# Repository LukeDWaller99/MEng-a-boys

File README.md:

## Contributions
**Luke Waller**

*Authored*

**Jack Pendlebury**

*Ripping everything except the ESCs out.*

# MEng-a-boys
MEng-a-boys

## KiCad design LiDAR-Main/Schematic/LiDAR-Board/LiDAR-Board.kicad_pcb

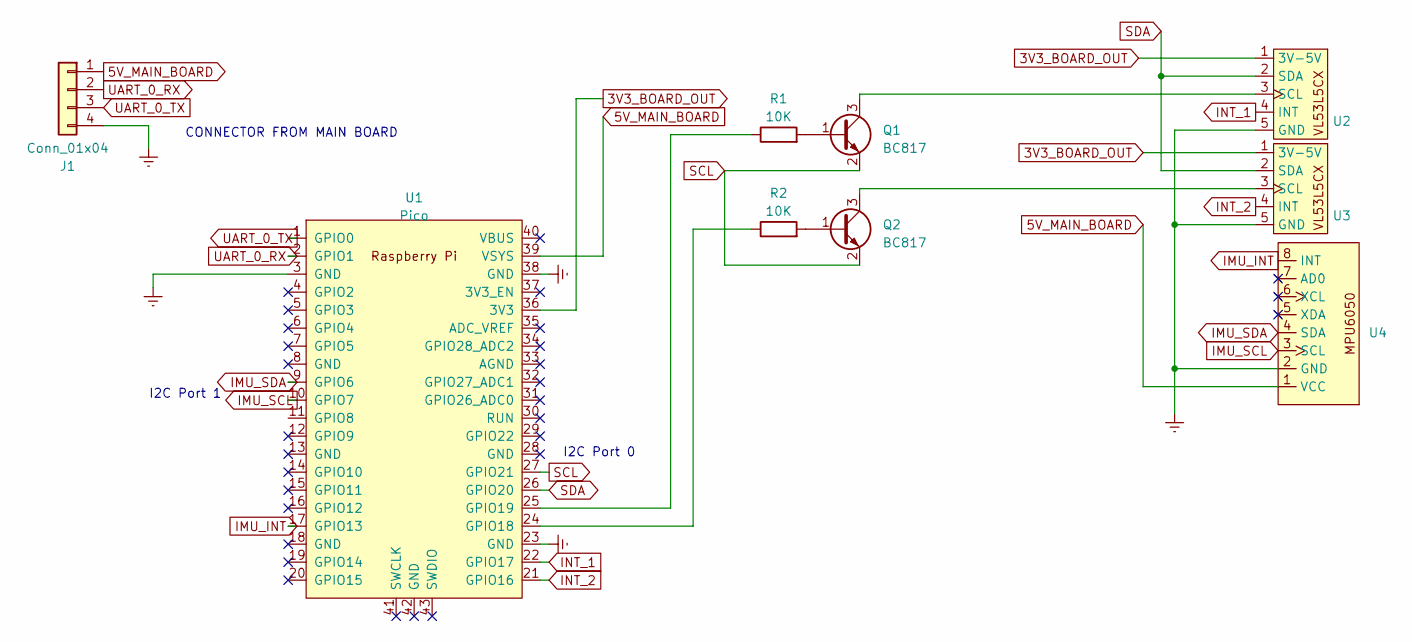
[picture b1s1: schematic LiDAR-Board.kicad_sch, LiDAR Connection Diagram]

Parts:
J1: Conn_01x04; Conn_01x04_MOLEX
Q1, Q2: BC817; SOT-23
R1, R2: 10K; R_0603_1608Metric
U1: Pico; Pi_Pico
U2, U3, U4: Conn_01x05_MOLEX

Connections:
3V3_BOARD_OUT: U1.36 (3V3), U2.1 (3V-5V), U3.1 (3V-5V)
5V_MAIN_BOARD: J1.1, U1.39 (VSYS), U4.1 (VCC)
Earth: J1.4, U1.3 (GND), U1.23 (GND), U1.38 (GND), U2.5 (GND), U3.5 (GND), U4.2 (GND)
IMU_INT: U1.17 (GPIO13), U4.8 (INT)
IMU_SCL: U1.10 (GPIO7), U4.3 (SCL)
IMU_SDA: U1.9 (GPIO6), U4.4 (SDA)
INT_1: U1.22 (GPIO17), U2.4 (INT)
INT_2: U1.21 (GPIO16), U3.4 (INT)
unnamed: Q1.1 (B), R1.2
unnamed: Q1.3 (C), U2.3 (SCL)
unnamed: Q2.1 (B), R2.2
unnamed: Q2.3 (C), U3.3 (SCL)
unnamed: R2.1, U1.24 (GPIO18)
unnamed: R1.1, U1.25 (GPIO19)
SCL: Q1.2 (E), Q2.2 (E), U1.27 (GPIO21)
SDA: U1.26 (GPIO20), U2.2 (SDA), U3.2 (SDA)
UART_0_RX: J1.2, U1.2 (GPIO1)
UART_0_TX: J1.3, U1.1 (GPIO0)

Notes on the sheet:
CONNECTOR FROM MAIN BOARD
I2C Port 1
I2C Port 0

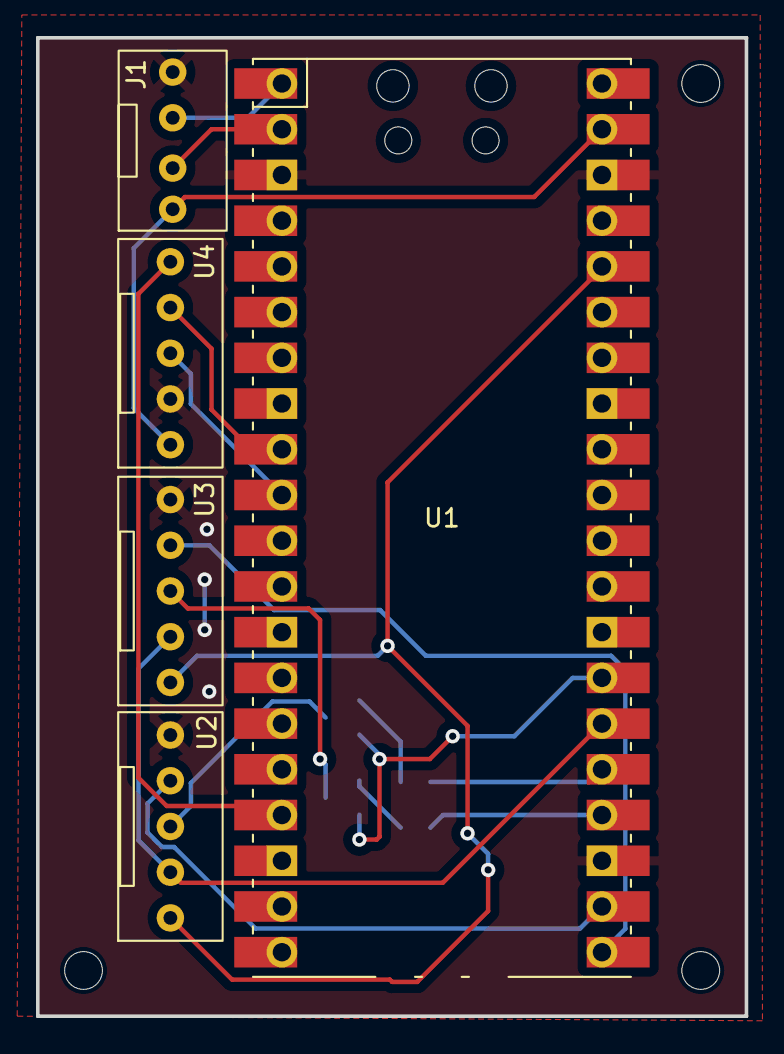
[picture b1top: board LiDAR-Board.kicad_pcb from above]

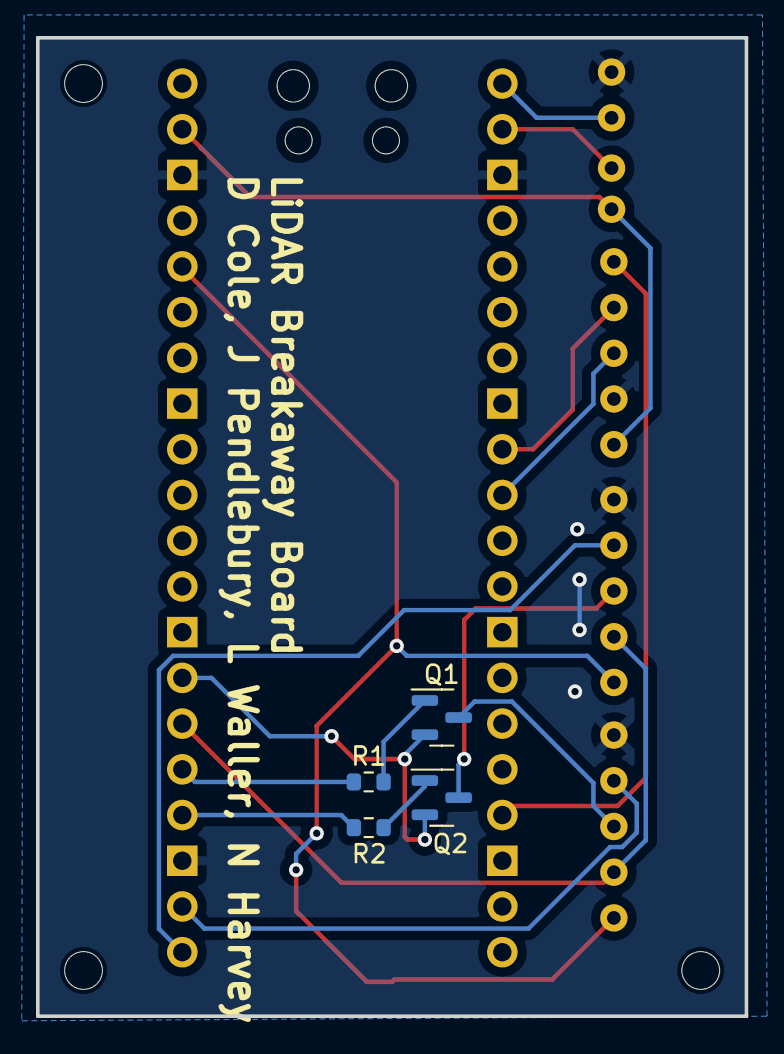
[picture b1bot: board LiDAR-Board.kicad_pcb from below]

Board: 2 copper layers, 39.4 x 54.4 mm, 9 parts (4 on the bottom side), 18 nets.

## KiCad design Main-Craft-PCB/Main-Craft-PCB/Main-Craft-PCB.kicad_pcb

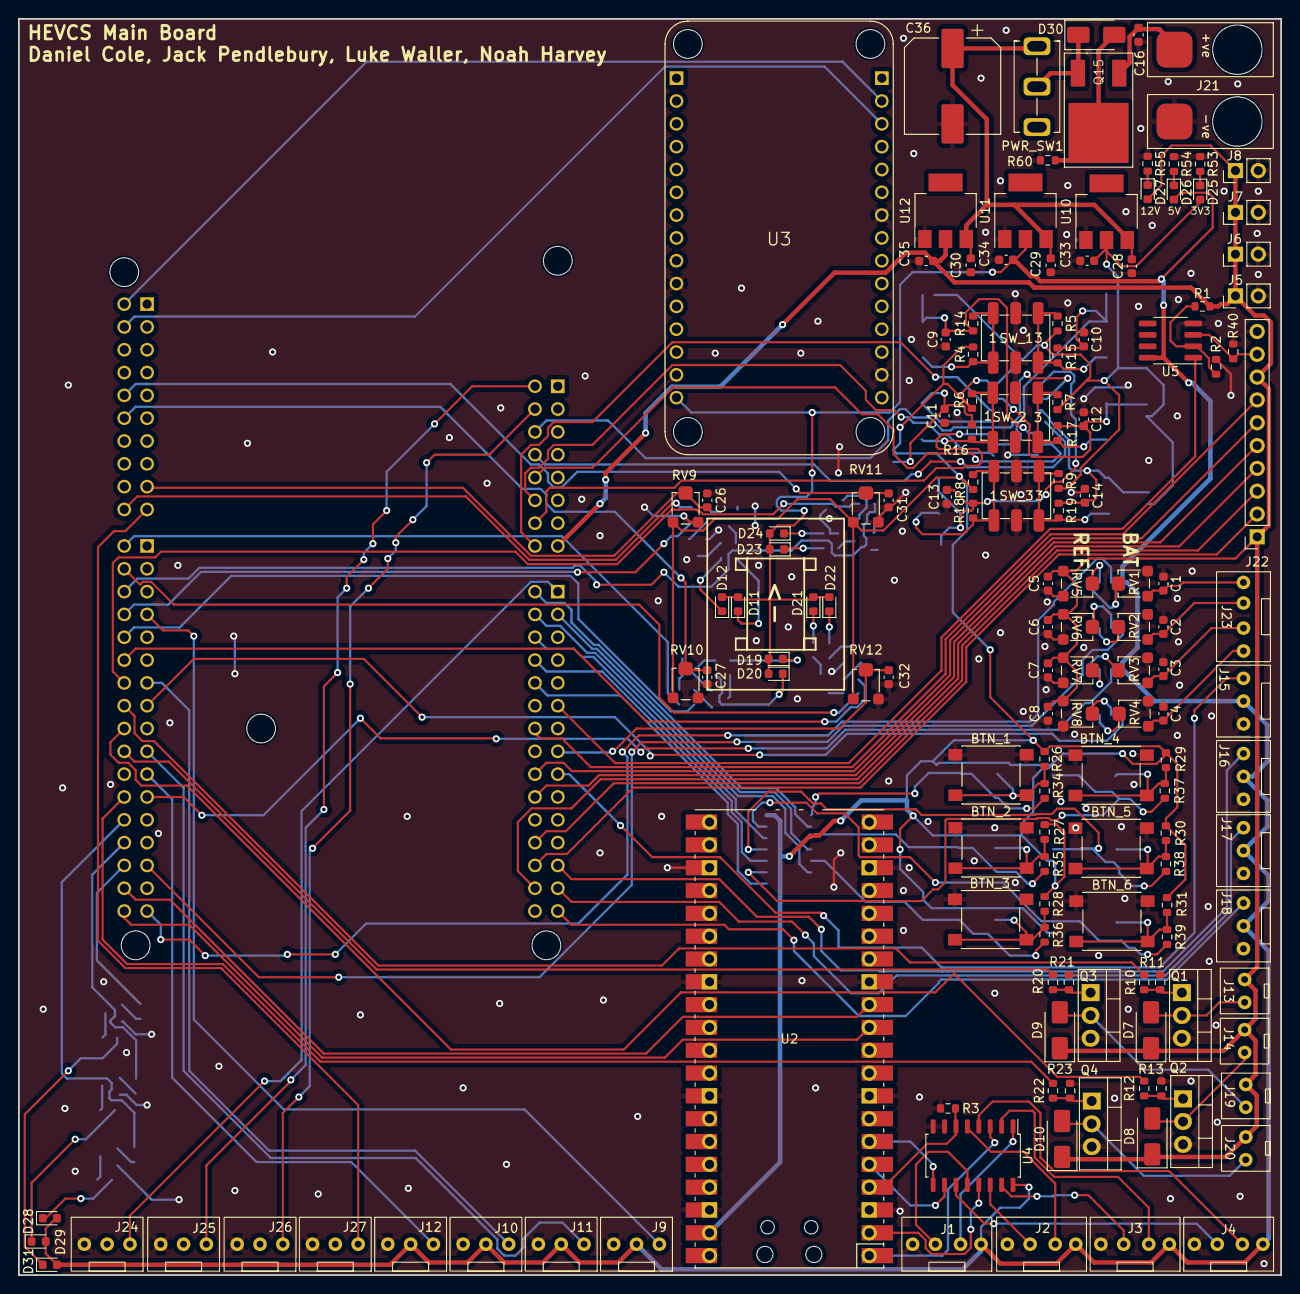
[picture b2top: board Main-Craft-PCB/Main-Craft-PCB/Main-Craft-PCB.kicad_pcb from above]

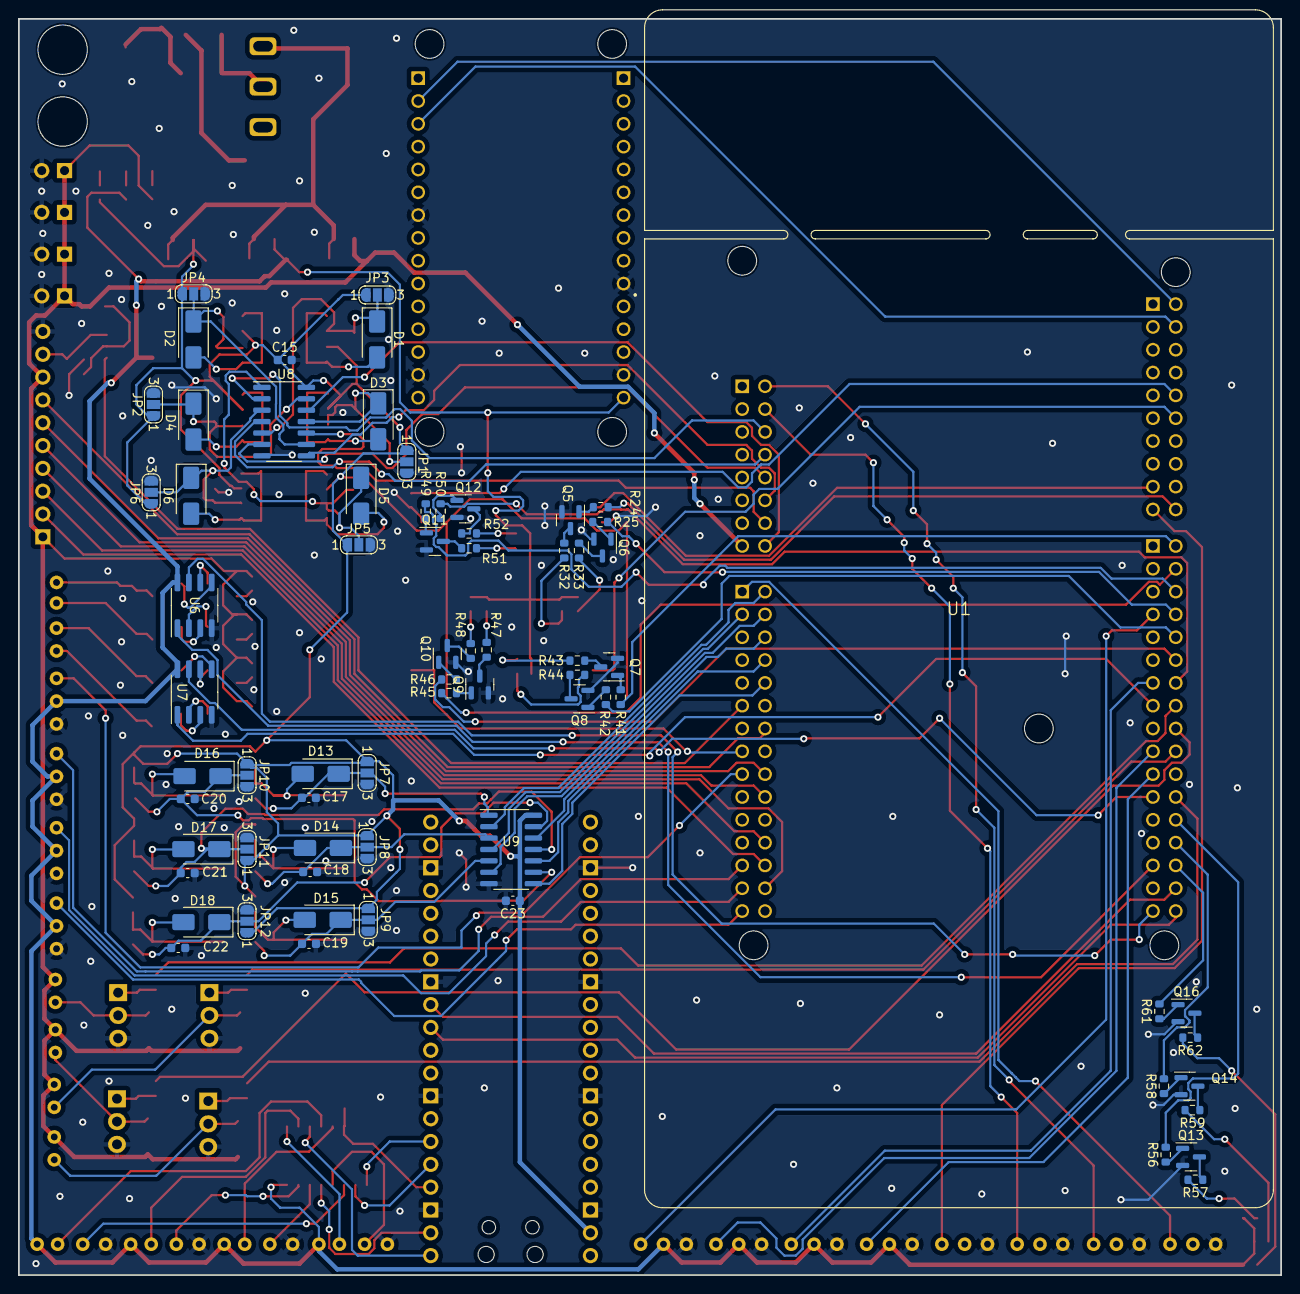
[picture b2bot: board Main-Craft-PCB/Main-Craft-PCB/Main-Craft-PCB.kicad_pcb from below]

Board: 2 copper layers, 140.5 x 139.8 mm, 216 parts (70 on the bottom side), 107 nets.

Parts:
BTN_1, BTN_2, BTN_3, BTN_4, BTN_5, BTN_6: SW_SPST; SW_Push_1P1T_NO_6x6mm_H9.5mm
C1, C2, C3, C4, C5, C6, C7, C8, C9, C10, C11, C12, C13, C14, C15, C16, C17, C18, C19, C20, C21, C22, C23, C26, C27, C28, C29, C30, C31, C32, C33, C34, C35: 100nF; C_0603_1608Metric
C36: 470uF; CP_Elec_10x10.5
D1, D2, D3, D4, D5, D6, D7, D8, D9, D10, D13, D14, D15, D16, D17, D18, D30: D; D_SMA
D11, D12, D19, D20, D21, D22, D23, D24, D27: RED; LED_0603_1608Metric
D25, D29: YELLOW; LED_0603_1608Metric
D26, D31: BLUE; LED_0603_1608Metric
D28: GREEN; LED_0603_1608Metric
J1: UART_1; Conn_01x04_MOLEX
J2: UART_2; Conn_01x04_MOLEX
J3: UART_3; Conn_01x04_MOLEX
J4: UART_4; Conn_01x04_MOLEX
J5, J6, J7, J8: LEDS; PinHeader_1x02_P2.54mm_Vertical
J9: S500_1; Conn_01x03_MOLEX
J10: S500_2; Conn_01x03_MOLEX
J11: S500_3; Conn_01x03_MOLEX
J12: S500_4; Conn_01x03_MOLEX
J13: SOL_1; Conn_01x02_MOLEX
J14: SOL_2; Conn_01x02_MOLEX
J15: RELAY_1; Conn_01x03_MOLEX
J16: RELAY_2; Conn_01x03_MOLEX
J17, J18: RELAY_3; Conn_01x03_MOLEX
J19: SOL_3; Conn_01x02_MOLEX
J20: SOL_4; Conn_01x02_MOLEX
J21: PWR_IN; 12AWG_PWR_IN
J22: Conn_01x10; PinSocket_1x10_P2.54mm_Vertical
J23: BAT_IN; Conn_01x04_MOLEX
J24: VESC_1; Conn_01x03_MOLEX
J25: VESC_2; Conn_01x03_MOLEX
J26: VESC_3; Conn_01x03_MOLEX
J27: VESC_4; Conn_01x03_MOLEX
JP1, JP2, JP3, JP4, JP5, JP6: JP; SolderJumper-3_P1.3mm_Open_RoundedPad1.0x1.5mm_NumberLabels
JP7, JP8, JP9, JP10, JP11, JP12: SolderJumper_3_Open; SolderJumper-3_P1.3mm_Open_RoundedPad1.0x1.5mm_NumberLabels
PWR_SW1: SW_SPDT; KNX-1-D1
Q1, Q2, Q3, Q4: TIP120; TO-220-3_Vertical
Q5, Q6, Q7, Q8, Q9, Q10, Q11, Q12, Q13, Q14, Q16: BC817; SOT-23
Q15: IRFR9014PBF; STD20NF06L
R1, R2, R54, R57, R62: 1K; R_0603_1608Metric
R3: 100K; R_0603_1608Metric
R4, R5, R6, R7, R8, R9, R11, R13, R14, R15, R16, R17, R18, R19, R21, R23, R26, R27, R28, R29, R30, R31, R34, R35, R36, R37, R38, R39, R40: 47K; R_0603_1608Metric
R10, R12, R20, R22, R53, R59: 2K2; R_0603_1608Metric
R24, R25, R41, R42, R45, R46, R49, R50, R56, R58, R61: 4K7; R_0603_1608Metric
R32, R33, R43, R44, R47, R48, R51, R52, R55: 150R; R_0603_1608Metric
R60: 100R; R_0603_1608Metric
RV1, RV2, RV3, RV4, RV5, RV6, RV7, RV8, RV9, RV10, RV11, RV12: 20K; Variable_Resistor
SW_1, SW_2, SW_3: SW; JS202011SCQN
U1: NUCLEO144-F429ZI; MODULE_NUCLEO-F429ZI
U2: Pi Pico; pi_pico
U3: ESP8266; ESP-8266
U4: SN74LV4052; SOIC-16_4.55x10.3mm_P1.27mm
U5, U6, U7: LM358DR2G; SOP-8_3.76x4.96mm_P1.27mm
U8, U9: 74HC14; SO-14_3.9x8.65mm_P1.27mm
U10: ZSR330GTA; SOT-223
U11: ZLDO1117G50TA; SOT-223
U12: BFU590GX; SOT-223

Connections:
12V_INPUT: C16.1, J21.1, Q15.1 (D)
+3V3: C15.1, C23.1, C33.2, D25.2 (A), JP1.1 (A), JP2.1 (A), JP3.1 (A), JP4.1 (A), JP5.1 (A), JP6.1 (A), JP7.1 (A), JP8.1 (A), JP9.1 (A), JP10.1 (A), JP11.1 (A), JP12.1 (A), R4.2, R5.2, R6.2, R7.2, R8.2, R9.2, R26.2, R27.2, R28.2, R29.2, R30.2, R31.2, RV9.1, RV10.1, RV11.1, RV12.1, U2.39 (VSYS), U8.14 (VCC), U9.14 (VCC), U10.2 (VO)
+5V: C34.2, D11.2 (A), D12.2 (A), D19.2 (A), D20.2 (A), D21.2 (A), D22.2 (A), D23.2 (A), D24.2 (A), D26.2 (A), D28.2 (A), D29.2 (A), D31.2 (A), J1.1, J2.1, J3.1, J4.1, J9.2, J10.2, J11.2, J12.2, J15.2, J16.2, J17.2, J18.2, U3.15 (Vin), U4.16 (VCC), U5.8 (V+), U6.8 (V+), U7.8 (V+), U11.2 (VO)
+12V: C5.1, C6.1, C7.1, C8.1, C35.2, D7.1 (K), D8.1 (K), D9.1 (K), D10.1 (K), D27.2 (A), J5.1, J6.1, J7.1, J8.1, J13.1, J14.1, J19.1, J20.1, J22.1, J22.8, R1.2, RV5.1, RV6.1, RV7.1, RV8.1, U12.2 (VO)
/X0: J1.3, U4.12 (X0)
/X1: J2.3, U4.14 (X1)
/X2: J3.3, U4.15 (X2)
/X3: J4.3, U4.11 (X3)
/Y0: J1.2, U4.1 (Y0)
/Y1: J2.2, U4.5 (Y1)
/Y2: J3.2, U4.2 (Y2)
/Y3: J4.2, U4.4 (Y3)
BATT_1_IN: C4.1, J23.4, RV4.1
BATT_2_IN: C3.1, J23.3, RV3.1
BATT_3_IN: C2.1, J23.2, RV2.1
BATT_4_IN: C1.1, J23.1, RV1.1
BTN_1_SB: C17.2, D13.1 (K), JP7.2 (C), R34.1, U9.1
BTN_2_SB: C18.2, D14.1 (K), JP8.2 (C), R35.1, U9.3
BTN_3_SB: C19.2, D15.1 (K), JP9.2 (C), R36.1, U9.5
BTN_4_SB: C20.2, D16.1 (K), JP10.2 (C), R37.1, U9.9
BTN_5_SB: C21.2, D17.1 (K), JP11.2 (C), R38.1, U9.11
BTN_6_SB: C22.2, D18.1 (K), JP12.2 (C), R39.1, U9.13
CON_CONNECTION: J22.9, R40.1, U5.3 (+)
Earth: BTN_1.1 (A), BTN_2.1 (A), BTN_3.1 (A), BTN_4.1 (A), BTN_5.1 (A), BTN_6.1 (A), C1.2, C2.2, C3.2, C4.2, C5.2, C6.2, C7.2, C8.2, C9.1, C10.1, C11.1, C12.1, C13.1, C14.1, C15.2, C16.2, C17.1, C18.1, C19.1, C20.1, C21.1, C22.1, C23.2, C26.2, C27.2, C28.2, C29.2, C30.2, C31.2, C32.2, C33.1, C34.1, C35.1, C36.2, J1.4, J2.4, J3.4, J4.4, J5.2, J6.2, J7.2, J8.2, J9.3, J10.3, J11.3, J12.3, J15.3, J16.3, J17.3, J18.3, J21.2, J22.10, J24.3, J25.3, J26.3, J27.3, JP1.3 (B), JP2.3 (B), JP3.3 (B), JP4.3 (B), JP5.3 (B), JP6.3 (B), JP7.3 (B), JP8.3 (B), JP9.3 (B), JP10.3 (B), JP11.3 (B), JP12.3 (B), Q1.3 (E), Q2.3 (E), Q3.3 (E), Q4.3 (E), Q5.2 (E), Q6.2 (E), Q7.2 (E), Q8.2 (E), Q9.2 (E), Q10.2 (E), Q11.2 (E), Q12.2 (E), Q13.2 (E), Q14.2 (E), Q16.2 (E), R2.1, R3.1, R11.1, R13.1, R21.1, R23.1, R40.2, R53.1, R54.1, R55.1, R60.2, RV1.3, RV2.3, RV3.3, RV4.3, RV5.3, RV6.3, RV7.3, RV8.3, RV9.3, RV10.3, RV11.3, RV12.3, SW_1.2, SW_2.2, SW_3.2, U2.3 (GND), U2.8 (GND), U2.13 (GND), U2.18 (GND), U2.23 (GND), U2.28 (GND), U2.33 (GND), U2.38 (GND), U3.10 (GND), U3.14 (GND), U3.17 (GND), U3.24 (GND), U4.7 (GND), U4.8 (GND), U5.4 (V-), U6.4 (V-), U7.4 (V-), U8.7 (GND), U9.7 (GND), U10.1 (GND), U11.1 (GND), U12.1 (GND)
unnamed: BTN_1.2 (B), D13.2 (A), R26.1, R34.2
unnamed: BTN_2.2 (B), D14.2 (A), R27.1, R35.2
unnamed: BTN_3.2 (B), D15.2 (A), R28.1, R36.2
unnamed: BTN_4.2 (B), D16.2 (A), R29.1, R37.2
unnamed: BTN_5.2 (B), D17.2 (A), R30.1, R38.2
unnamed: BTN_6.2 (B), D18.2 (A), R31.1, R39.2
unnamed: D1.2 (A), R4.1, R14.2, SW_1.1
unnamed: D2.2 (A), R5.1, R15.2, SW_1.3
unnamed: D3.2 (A), R6.1, R16.2, SW_2.1
unnamed: D4.2 (A), R7.1, R17.2, SW_2.3
unnamed: D5.2 (A), R8.1, R18.2, SW_3.1
unnamed: D6.2 (A), R9.1, R19.2, SW_3.3
unnamed: D7.2 (A), J13.2, Q1.2 (C)
unnamed: D8.2 (A), J14.2, Q2.2 (C)
unnamed: D9.2 (A), J19.2, Q3.2 (C)
unnamed: D10.2 (A), J20.2, Q4.2 (C)
unnamed: D11.1 (K), R32.2
unnamed: D12.1 (K), R33.2
unnamed: D19.1 (K), R43.2
unnamed: D20.1 (K), R44.2
unnamed: D21.1 (K), R47.2
unnamed: D22.1 (K), R48.2
unnamed: D23.1 (K), R51.2
unnamed: D24.1 (K), R52.2
unnamed: D25.1 (K), R53.2
unnamed: D26.1 (K), R54.2
unnamed: D27.1 (K), R55.2
unnamed: D28.1 (K), R57.2
unnamed: D29.1 (K), R59.2
unnamed: D30.2 (A), Q15.2 (G), R60.1
unnamed: D30.1 (K), PWR_SW1.2 (B), Q15.3 (S)
unnamed: D31.1 (K), R62.2
unnamed: Q1.1 (B), R10.2, R11.2
unnamed: Q2.1 (B), R12.2, R13.2
unnamed: Q3.1 (B), R20.2, R21.2
unnamed: Q4.1 (B), R22.2, R23.2
unnamed: Q5.1 (B), R24.1
unnamed: Q5.3 (C), R32.1
unnamed: Q6.1 (B), R25.1
unnamed: Q6.3 (C), R33.1
unnamed: Q7.1 (B), R41.1
unnamed: Q7.3 (C), R43.1
unnamed: Q8.1 (B), R42.1
unnamed: Q8.3 (C), R44.1
unnamed: Q9.1 (B), R45.1
unnamed: Q9.3 (C), R47.1
unnamed: Q10.1 (B), R46.1
unnamed: Q10.3 (C), R48.1
unnamed: Q11.1 (B), R49.1
unnamed: Q11.3 (C), R51.1
unnamed: Q12.1 (B), R50.1
unnamed: Q12.3 (C), R52.1
unnamed: Q13.1 (B), R56.1
unnamed: Q13.3 (C), R57.1
unnamed: Q14.1 (B), R58.1
unnamed: Q14.3 (C), R59.1
unnamed: Q16.1 (B), R61.1
unnamed: Q16.3 (C), R62.1
unnamed: R1.1, R2.2, U5.2 (-)
unnamed: RV2.2, U6.3 (+)
unnamed: RV6.2, U6.2 (-)
unnamed: RV1.2, U6.5 (+)
unnamed: RV5.2, U6.6 (-)
unnamed: RV4.2, U7.3 (+)
unnamed: RV8.2, U7.2 (-)
unnamed: RV3.2, U7.5 (+)
unnamed: RV7.2, U7.6 (-)
PICO_INH: R3.2, U2.4 (GP2), U4.6 (INH)
PICO_RX: U2.2 (GP1), U4.13 (X-COM)
PICO_TX: U2.1 (GPO), U4.3 (Y-COM)
SW_1_DOWN_SB: C14.2, D6.1 (K), JP6.2 (C), R19.1, U8.3
SW_1_UP_SB: C13.2, D5.1 (K), JP5.2 (C), R18.1, U8.1
SW_2_DOWN_SB: C10.2, D2.1 (K), JP4.2 (C), R15.1, U8.9
SW_2_UP_SB: C9.2, D1.1 (K), JP3.2 (C), R14.1, U8.5
SW_3_DOWN_SB: C12.2, D4.1 (K), JP2.2 (C), R17.1, U8.13
SW_3_UP_SB: C11.2, D3.1 (K), JP1.2 (C), R16.1, U8.11
TRIM_POT_1: C26.1, RV9.2
TRIM_POT_2: C31.1, RV11.2
TRIM_POT_3: C27.1, RV10.2
TRIM_POT_4: C32.1, RV12.2
UART_EN_A: U2.5 (GP3), U4.10 (A)
UART_EN_B: U2.6 (GP4), U4.9 (B)
VIN: C28.1, C29.1, C30.1, C36.1, PWR_SW1.1 (A), U10.3 (VI), U11.3 (VI), U12.3 (VI)

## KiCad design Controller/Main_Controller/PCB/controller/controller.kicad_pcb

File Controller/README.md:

# Controller Specifications
----
## Requirements
The Controller will need to remotely control the craft with bi-directional communication. This will involve serveral design considerations including:
1. [x] Microcontroller
	1. [x] NUCELO-L432KC
2. [x] Inputs
	1. [x] 2 Analogue Joysticks
	2. [x] 4 buttons
		1. [x] 3 discreet buttons
		2. [x] Reset Button
	3. [x] 1 SPDT toggling switches
3. [x] Outputs
	1. [x] Buzzer for feedback to user
	2. [x] 1 Status LEDs
4. [ ] Power
	1. [x] Power Indicator LEDs
	2. [ ] Battery Powered
		1. [ ] 18650 Li-Po battery
		2. [ ] Battery Charger
	3. [ ] Suitable Buck Converter to supply appropriate voltages
	4. [ ] Reverse polarity protection
	5. [ ] Low voltage detection chip
	6. [x] ON/OFF power switch
5. [ ] Communication with main craft
	1. [x] RF chip (nRF24L01)
	2. [ ] Bi-directional communication
6. [ ] Case
	1. [ ] Comfortable
	2. [ ] Ergonomic 
	3. [ ] Light and easy to tranport 
	4. [ ] 3D printed
	5. [ ] Easy to use
7. [ ] PCB/Electronics
	1. [x] Schematic  
	2. [ ] PCB Layout
8. [ ] Testing
	1. [x] Testing individual assemblies on a breadboard
	2. [ ] Debugging code to test all individual components on the PCB

## Dependancies/Libraries Used

`nRF24L01P.h` Authored by Owen Edwards (c) 2010 (Modified by Luke Waller - 2022)
----
## Contributions
**Luke Waller**

*Authored*

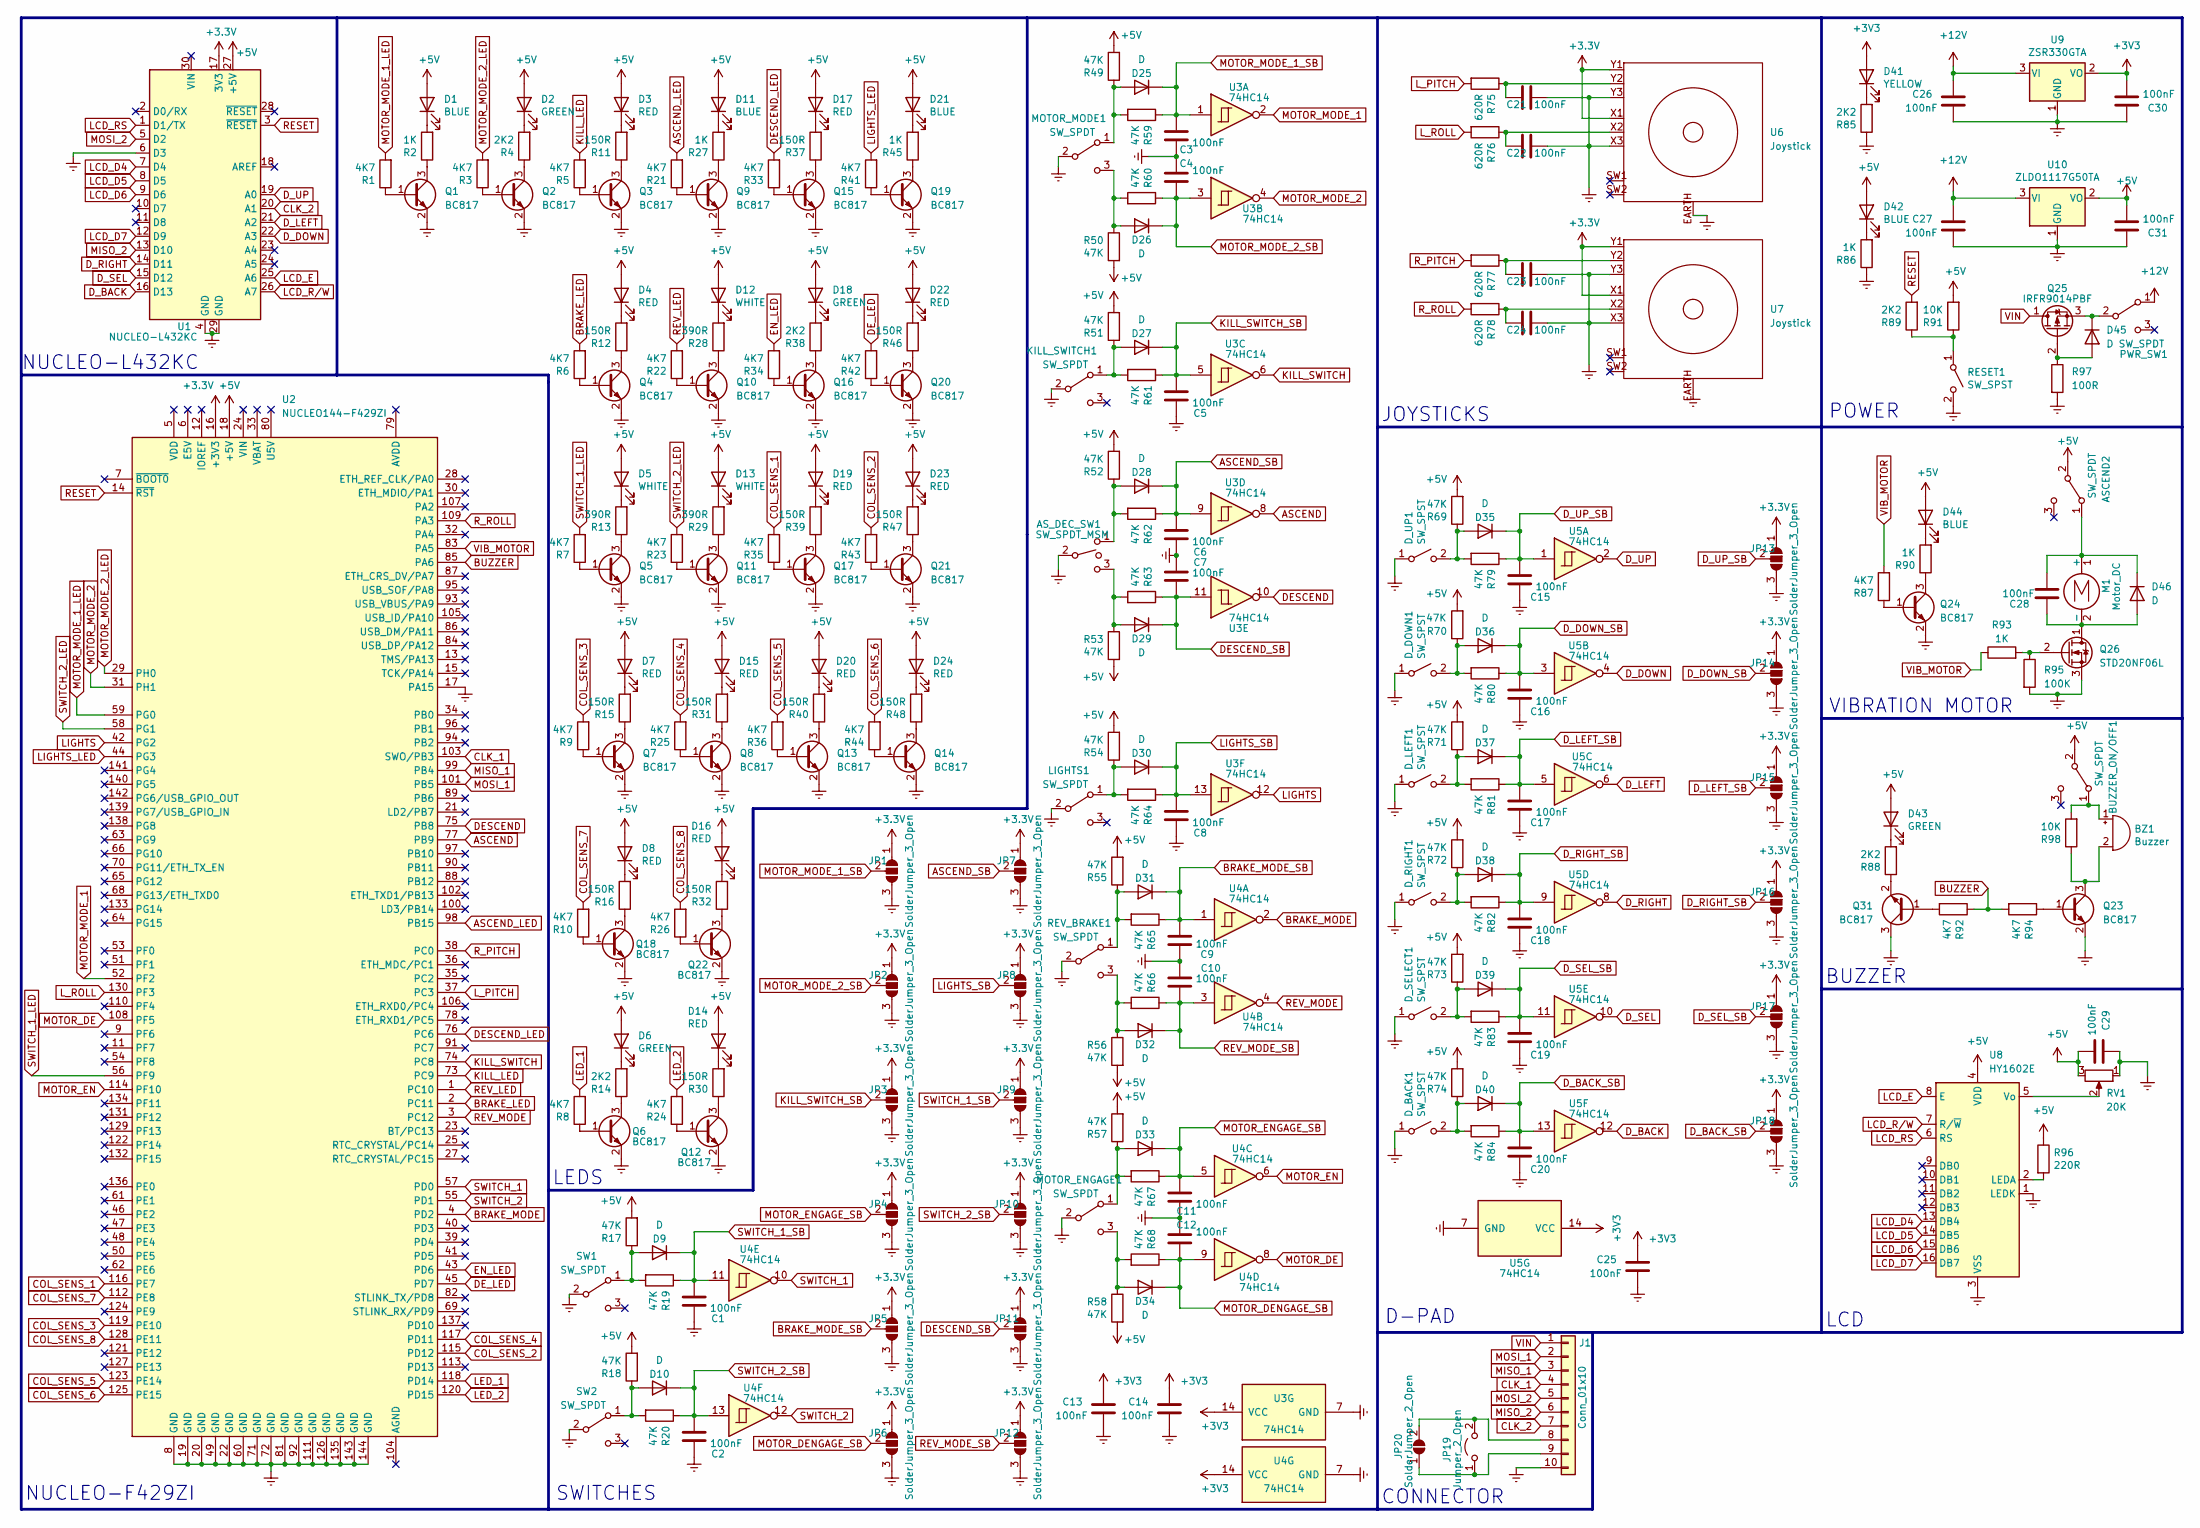
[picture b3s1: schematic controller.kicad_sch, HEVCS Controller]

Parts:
ASCEND2: SW_SPDT; 1Ms1T1B1M1QE
AS_DEC_SW1: SW_SPDT_MSM; 1Ms1T1B1M1QE
BUZZER_ON/OFF1: SW_SPDT; 1Ms1T1B1M1QE
BZ1: Buzzer
C1, C2, C3, C4, C5, C6, C7, C8, C9, C10, C11, C12, C13, C14, C15, C16, C17, C18, C19, C20, C21, C22, C23, C24, C25, C26, C27, C28, C29, C30, C31: 100nF; C_0603_1608Metric
D1, D11, D21, D42, D44: BLUE; LED_0603_1608Metric
D2, D6, D18, D43: GREEN; LED_0603_1608Metric
D3, D4, D7, D8, D14, D15, D16, D17, D19, D20, D22, D23, D24: RED; LED_0603_1608Metric
D5, D12, D13: WHITE; LED_0603_1608Metric
D9, D10, D25, D26, D27, D28, D29, D30, D31, D32, D33, D34, D35, D36, D37, D38, D39, D40, D45, D46: D; D_SMA
D41: YELLOW; LED_0603_1608Metric
D_BACK1: SW_SPST; SW_Push_1P1T_NO_6x6mm_H9.5mm
D_DOWN1: SW_SPST; SW_Push_1P1T_NO_6x6mm_H9.5mm
D_LEFT1: SW_SPST; SW_Push_1P1T_NO_6x6mm_H9.5mm
D_RIGHT1: SW_SPST; SW_Push_1P1T_NO_6x6mm_H9.5mm
D_SELECT1: SW_SPST; SW_Push_1P1T_NO_6x6mm_H9.5mm
D_UP1: SW_SPST; SW_Push_1P1T_NO_6x6mm_H9.5mm
J1: Conn_01x10; PinHeader_1x10_P1.27mm_Vertical
JP1, JP2, JP3, JP4, JP5, JP6, JP7, JP8, JP9, JP10, JP11, JP12, JP13, JP14, JP15, JP16, JP17, JP18: SolderJumper_3_Open; SolderJumper-3_P1.3mm_Open_RoundedPad1.0x1.5mm_NumberLabels
JP19: Jumper_2_Open
JP20: SolderJumper_2_Open
KILL_SWITCH1: SW_SPDT; 1Ms1T1B1M1QE
LIGHTS1: SW_SPDT; 1Ms1T1B1M1QE
M1: Motor_DC; Vybronics_VZ30C1T8219732L
MOTOR_ENGAGE1: SW_SPDT; 1Ms1T1B1M1QE
MOTOR_MODE1: SW_SPDT; 1Ms1T1B1M1QE
PWR_SW1: SW_SPDT; KNX-1-D1
Q1, Q2, Q3, Q4, Q5, Q6, Q7, Q8, Q9, Q10, Q11, Q12, Q13, Q14, Q15, Q16, Q17, Q18, Q19, Q20, Q21, Q22, Q23, Q24, Q31: BC817; SOT-23
Q25: IRFR9014PBF; STD20NF06L
Q26: STD20NF06L
R1, R3, R5, R6, R7, R8, R9, R10, R21, R22, R23, R24, R25, R26, R33, R34, R35, R36, R41, R42, R43, R44, R87, R92, R94: 4K7; R_0603_1608Metric
R2, R27, R45, R86, R90, R93: 1K; R_0603_1608Metric
R4, R14, R38, R85, R88, R89: 2K2; R_0603_1608Metric
R11, R12, R15, R16, R30, R31, R32, R37, R39, R40, R46, R47, R48: 150R; R_0603_1608Metric
R13, R28, R29: 390R; R_0603_1608Metric
R17, R18, R19, R20, R49, R50, R51, R52, R53, R54, R55, R56, R57, R58, R59, R60, R61, R62, R63, R64, R65, R66, R67, R68, R69, R70, R71, R72, R73, R74, R79, R80, R81, R82, R83, R84: 47K; R_0603_1608Metric
R75, R76, R77, R78: 620R; R_0603_1608Metric
R91, R98: 10K; R_0603_1608Metric
R95: 100K; R_0603_1608Metric
R96: 220R; R_0603_1608Metric
R97: 100R; R_0603_1608Metric
RESET1: SW_SPST; SW_Push_1P1T_NO_6x6mm_H9.5mm
REV_BRAKE1: SW_SPDT; 1Ms1T1B1M1QE
RV1: 20K; Variable_Resistor
SW1, SW2: SW_SPDT; 1Ms1T1B1M1QE
U1: NUCLEO-L432KC; Arduino_Nano
U2: NUCLEO144-F429ZI; MODULE_NUCLEO-F429ZI_JUST_PINS
U3, U4, U5: 74HC14; SO-14_3.9x8.65mm_P1.27mm
U6, U7: Joystick
U8: HY1602E; LCD_Display_WH1602B-NYG-JT
U9: ZSR330GTA; SOT-223
U10: ZLDO1117G50TA; SOT-223

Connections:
+5V: ASCEND2.2 (B), BUZZER_ON/OFF1.2 (B), C29.2, C31.2, D1.2 (A), D2.2 (A), D3.2 (A), D4.2 (A), D5.2 (A), D6.2 (A), D7.2 (A), D8.2 (A), D11.2 (A), D12.2 (A), D13.2 (A), D14.2 (A), D15.2 (A), D16.2 (A), D17.2 (A), D18.2 (A), D19.2 (A), D20.2 (A), D21.2 (A), D22.2 (A), D23.2 (A), D24.2 (A), D42.2 (A), D43.2 (A), D44.2 (A), R17.2, R18.2, R49.2, R50.2, R51.2, R52.2, R53.2, R54.2, R55.2, R56.2, R57.2, R58.2, R69.2, R70.2, R71.2, R72.2, R73.2, R74.2, R91.2, R96.1, RV1.3, U1.27 (+5V), U2.18 (+5V), U8.4 (VDD), U10.2 (VO)
+12V: C26.1, C27.1, PWR_SW1.1 (A), U9.3 (VI), U10.3 (VI)
ASCEND: U2.77 (PB9), U3.8
ASCEND_LED: R21.2, U2.98 (PB15)
ASCEND_SB: C6.2, D28.1 (K), JP7.2 (C), R62.1, U3.9
BRAKE_LED: R6.2, U2.2 (PC11)
BRAKE_MODE: U2.4 (PD2), U4.2
BRAKE_MODE_SB: C9.2, D31.1 (K), JP5.2 (C), R65.1, U4.1
BUZZER: R92.1, R94.2, U2.85 (PA6)
CLK_1: J1.4, U2.103 (SWO/PB3)
CLK_2: J1.7, U1.20 (A1)
COL_SENS_1: R35.2, U2.116 (PE7)
COL_SENS_2: R43.2, U2.115 (PD12)
COL_SENS_3: R9.2, U2.119 (PE10)
COL_SENS_4: R25.2, U2.117 (PD11)
COL_SENS_5: R36.2, U2.123 (PE14)
COL_SENS_6: R44.2, U2.125 (PE15)
COL_SENS_7: R10.2, U2.112 (PE8)
COL_SENS_8: R26.2, U2.128 (PE11)
DESCEND: U2.75 (PB8), U3.10
DESCEND_LED: R33.2, U2.76 (PC6)
DESCEND_SB: C7.2, D29.1 (K), JP11.2 (C), R63.1, U3.11
DE_LED: R42.2, U2.45 (PD7)
D_BACK: U1.16 (D13), U5.12
D_BACK_SB: C20.2, D40.1 (K), JP18.2 (C), R84.1, U5.13
D_DOWN: U1.22 (A3), U5.4
D_DOWN_SB: C16.2, D36.1 (K), JP14.2 (C), R80.1, U5.3
D_LEFT: U1.21 (A2), U5.6
D_LEFT_SB: C17.2, D37.1 (K), JP15.2 (C), R81.1, U5.5
D_RIGHT: U1.14 (D11), U5.8
D_RIGHT_SB: C18.2, D38.1 (K), JP16.2 (C), R82.1, U5.9
D_SEL: U1.15 (D12), U5.10
D_SEL_SB: C19.2, D39.1 (K), JP17.2 (C), R83.1, U5.11
D_UP: U1.19 (A0), U5.2
D_UP_SB: C15.2, D35.1 (K), JP13.2 (C), R79.1, U5.1
EN_LED: R34.2, U2.43 (PD6)
Earth: AS_DEC_SW1.2, C1.1, C2.1, C3.1, C4.1, C5.1, C6.1, C7.1, C8.1, C9.1, C10.1, C11.1, C12.1, C13.2, C14.2, C15.1, C16.1, C17.1, C18.1, C19.1, C20.1, C21.1, C22.1, C23.1, C24.1, C25.2, C26.2, C27.2, C29.1, C30.1, C31.1, D_BACK1.1 (A), D_DOWN1.1 (A), D_LEFT1.1 (A), D_RIGHT1.1 (A), D_SELECT1.1 (A), D_UP1.1 (A), J1.10, JP1.3 (B), JP2.3 (B), JP3.3 (B), JP4.3 (B), JP5.3 (B), JP6.3 (B), JP7.3 (B), JP8.3 (B), JP9.3 (B), JP10.3 (B), JP11.3 (B), JP12.3 (B), JP13.3 (B), JP14.3 (B), JP15.3 (B), JP16.3 (B), JP17.3 (B), JP18.3 (B), KILL_SWITCH1.2 (B), LIGHTS1.2 (B), MOTOR_ENGAGE1.2 (B), MOTOR_MODE1.2 (B), Q1.2 (E), Q2.2 (E), Q3.2 (E), Q4.2 (E), Q5.2 (E), Q6.2 (E), Q7.2 (E), Q8.2 (E), Q9.2 (E), Q10.2 (E), Q11.2 (E), Q12.2 (E), Q13.2 (E), Q14.2 (E), Q15.2 (E), Q16.2 (E), Q17.2 (E), Q18.2 (E), Q19.2 (E), Q20.2 (E), Q21.2 (E), Q22.2 (E), Q23.2 (E), Q24.2 (E), Q26.3 (S), Q31.3 (C), R85.1, R86.1, R95.2, R97.2, RESET1.2 (B), REV_BRAKE1.2 (B), RV1.1, SW1.2 (B), SW2.2 (B), U1.4 (GND), U1.6 (D3), U1.29 (GND), U2.8 (GND), U2.17 (PA15), U2.19 (GND), U2.20 (GND), U2.22 (GND), U2.49 (GND), U2.60 (GND), U2.71 (GND), U2.72 (GND), U2.81 (GND), U2.92 (GND), U2.111 (GND), U2.126 (GND), U2.135 (GND), U2.143 (GND), U2.144 (GND), U3.7 (GND), U4.7 (GND), U5.7 (GND), U6.EARTH, U6.X3, U6.Y3, U7.EARTH, U7.X3, U7.Y3, U8.1 (LEDK), U8.3 (VSS), U9.1 (GND), U10.1 (GND)
KILL_LED: R5.2, U2.73 (PC9)
KILL_SWITCH: U2.74 (PC8), U3.6
KILL_SWITCH_SB: C5.2, D27.1 (K), JP3.2 (C), R61.1, U3.5
LCD_D4: U1.7 (D4), U8.13 (DB4)
LCD_D5: U1.8 (D5), U8.14 (DB5)
LCD_D6: U1.9 (D6), U8.15 (DB6)
LCD_D7: U1.12 (D9), U8.16 (DB7)
LCD_E: U1.25 (A6), U8.8 (E)
LCD_RS: U1.1 (D1/TX), U8.6 (RS)
LCD_R/W: U1.26 (A7), U8.7 (R/~W)
LED_1: R8.2, U2.118 (PD14)
LED_2: R24.2, U2.120 (PD15)
LIGHTS: U2.42 (PG2), U3.12
LIGHTS_LED: R41.2, U2.44 (PG3)
LIGHTS_SB: C8.2, D30.1 (K), JP8.2 (C), R64.1, U3.13
L_PITCH: R75.2, U2.37 (PC3)
L_ROLL: R76.2, U2.130 (PF3)
MISO_1: J1.3, U2.99 (PB4)
MISO_2: J1.6, U1.13 (D10)
MOSI_1: J1.2, U2.101 (PB5)
MOSI_2: J1.5, U1.5 (D2)
MOTOR_DE: U2.108 (PF5), U4.8
MOTOR_DENGAGE_SB: C12.2, D34.1 (K), JP6.2 (C), R68.1, U4.9
MOTOR_EN: U2.114 (PF10), U4.6
MOTOR_ENGAGE_SB: C11.2, D33.1 (K), JP4.2 (C), R67.1, U4.5
MOTOR_MODE_1: U2.52 (PF2), U3.2
MOTOR_MODE_1_LED: R1.2, U2.59 (PG0)
MOTOR_MODE_1_SB: C3.2, D25.1 (K), JP1.2 (C), R59.1, U3.1
MOTOR_MODE_2: U2.31 (PH1), U3.4
MOTOR_MODE_2_LED: R3.2, U2.29 (PH0)
MOTOR_MODE_2_SB: C4.2, D26.1 (K), JP2.2 (C), R60.1, U3.3
unnamed: ASCEND2.1 (A), C28.2, D46.1 (K), M1.1 (+)
unnamed: BUZZER_ON/OFF1.1 (A), BZ1.1 (-), R98.2
unnamed: BZ1.2 (+), Q23.3 (C), R98.1
unnamed: C21.2, R75.1, U6.Y2
unnamed: C22.2, R76.1, U6.X2
unnamed: C23.2, R77.1, U7.Y2
unnamed: C24.2, R78.1, U7.X2
unnamed: D1.1 (K), R2.2
unnamed: D2.1 (K), R4.2
unnamed: D3.1 (K), R11.2
unnamed: D4.1 (K), R12.2
unnamed: D5.1 (K), R13.2
unnamed: D6.1 (K), R14.2
unnamed: D7.1 (K), R15.2
unnamed: D8.1 (K), R16.2
unnamed: D9.2 (A), R17.1, R19.2, SW1.1 (A)
unnamed: D10.2 (A), R18.1, R20.2, SW2.1 (A)
unnamed: D11.1 (K), R27.2
unnamed: D12.1 (K), R28.2
unnamed: D13.1 (K), R29.2
unnamed: D14.1 (K), R30.2
unnamed: D15.1 (K), R31.2
unnamed: D16.1 (K), R32.2
unnamed: D17.1 (K), R37.2
unnamed: D18.1 (K), R38.2
unnamed: D19.1 (K), R39.2
unnamed: D20.1 (K), R40.2
unnamed: D21.1 (K), R45.2
unnamed: D22.1 (K), R46.2
unnamed: D23.1 (K), R47.2
unnamed: D24.1 (K), R48.2
unnamed: D25.2 (A), MOTOR_MODE1.1 (A), R49.1, R59.2
unnamed: D26.2 (A), MOTOR_MODE1.3 (C), R50.1, R60.2
unnamed: D27.2 (A), KILL_SWITCH1.1 (A), R51.1, R61.2
unnamed: AS_DEC_SW1.1, D28.2 (A), R52.1, R62.2
unnamed: AS_DEC_SW1.3, D29.2 (A), R53.1, R63.2
unnamed: D30.2 (A), LIGHTS1.1 (A), R54.1, R64.2
unnamed: D31.2 (A), R55.1, R65.2, REV_BRAKE1.1 (A)
unnamed: D32.2 (A), R56.1, R66.2, REV_BRAKE1.3 (C)
unnamed: D33.2 (A), MOTOR_ENGAGE1.1 (A), R57.1, R67.2
unnamed: D34.2 (A), MOTOR_ENGAGE1.3 (C), R58.1, R68.2
unnamed: D35.2 (A), D_UP1.2 (B), R69.1, R79.2
unnamed: D36.2 (A), D_DOWN1.2 (B), R70.1, R80.2
unnamed: D37.2 (A), D_LEFT1.2 (B), R71.1, R81.2
unnamed: D38.2 (A), D_RIGHT1.2 (B), R72.1, R82.2
unnamed: D39.2 (A), D_SELECT1.2 (B), R73.1, R83.2
unnamed: D40.2 (A), D_BACK1.2 (B), R74.1, R84.2
unnamed: D41.1 (K), R85.2
unnamed: D42.1 (K), R86.2
unnamed: D43.1 (K), R88.2
unnamed: D44.1 (K), R90.2
unnamed: D45.2 (A), Q25.2 (G), R97.1
unnamed: D45.1 (K), PWR_SW1.2 (B), Q25.3 (S)
unnamed: C28.1, D46.2 (A), M1.2 (-), Q26.1 (D)
unnamed: J1.8, JP19.2 (B), JP20.2 (B)
unnamed: J1.9, JP19.1 (A), JP20.1 (A)
unnamed: Q1.1 (B), R1.1
unnamed: Q1.3 (C), R2.1
unnamed: Q2.1 (B), R3.1
unnamed: Q2.3 (C), R4.1
unnamed: Q3.1 (B), R5.1
unnamed: Q3.3 (C), R11.1
unnamed: Q4.1 (B), R6.1
unnamed: Q4.3 (C), R12.1
unnamed: Q5.1 (B), R7.1
unnamed: Q5.3 (C), R13.1
unnamed: Q6.1 (B), R8.1
unnamed: Q6.3 (C), R14.1
unnamed: Q7.1 (B), R9.1
unnamed: Q7.3 (C), R15.1
unnamed: Q8.1 (B), R25.1
unnamed: Q8.3 (C), R31.1
unnamed: Q9.1 (B), R21.1
unnamed: Q9.3 (C), R27.1
unnamed: Q10.1 (B), R22.1
unnamed: Q10.3 (C), R28.1
unnamed: Q11.1 (B), R23.1
unnamed: Q11.3 (C), R29.1
unnamed: Q12.1 (B), R24.1
unnamed: Q12.3 (C), R30.1
unnamed: Q13.1 (B), R36.1
unnamed: Q13.3 (C), R40.1
unnamed: Q14.1 (B), R44.1
unnamed: Q14.3 (C), R48.1
unnamed: Q15.1 (B), R33.1
unnamed: Q15.3 (C), R37.1
unnamed: Q16.1 (B), R34.1
unnamed: Q16.3 (C), R38.1
unnamed: Q17.1 (B), R35.1
unnamed: Q17.3 (C), R39.1
unnamed: Q18.1 (B), R10.1
unnamed: Q18.3 (C), R16.1
unnamed: Q19.1 (B), R41.1
unnamed: Q19.3 (C), R45.1
unnamed: Q20.1 (B), R42.1
unnamed: Q20.3 (C), R46.1
unnamed: Q21.1 (B), R43.1
unnamed: Q21.3 (C), R47.1
unnamed: Q22.1 (B), R26.1
unnamed: Q22.3 (C), R32.1
unnamed: Q23.1 (B), R94.1
unnamed: Q24.1 (B), R87.1
unnamed: Q24.3 (C), R90.1
unnamed: Q26.2 (G), R93.2, R95.1
unnamed: Q31.1 (B), R92.2
unnamed: Q31.2 (E), R88.1
unnamed: R89.1, R91.1, RESET1.1 (A)
unnamed: R96.2, U8.2 (LEDA)
unnamed: RV1.2, U8.5 (Vo)
RESET: R89.2, U1.3 (~RESET), U2.14 (~RST)
REV_LED: R22.2, U2.1 (PC10)
REV_MODE: U2.3 (PC12), U4.4
REV_MODE_SB: C10.2, D32.1 (K), JP12.2 (C), R66.1, U4.3
R_PITCH: R77.2, U2.38 (PC0)
R_ROLL: R78.2, U2.109 (PA3)
SWITCH_1: U2.57 (PD0), U4.10
SWITCH_1_LED: R7.2, U2.56 (PF9)
SWITCH_1_SB: C1.2, D9.1 (K), JP9.2 (C), R19.1, U4.11
SWITCH_2: U2.55 (PD1), U4.12
SWITCH_2_LED: R23.2, U2.58 (PG1)
SWITCH_2_SB: C2.2, D10.1 (K), JP10.2 (C), R20.1, U4.13
VIB_MOTOR: R87.2, R93.1, U2.83 (PA5)
VIN: J1.1, Q25.1 (D)

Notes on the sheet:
POWER
NUCLEO-F429ZI
LEDS
JOYSTICKS
CONNECTOR
BUZZER
VIBRATION MOTOR
SWITCHES
NUCLEO-L432KC
D-PAD
LCD

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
